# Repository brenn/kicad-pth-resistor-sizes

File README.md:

Simple PCB with PTH resistor sizes, for kicad work

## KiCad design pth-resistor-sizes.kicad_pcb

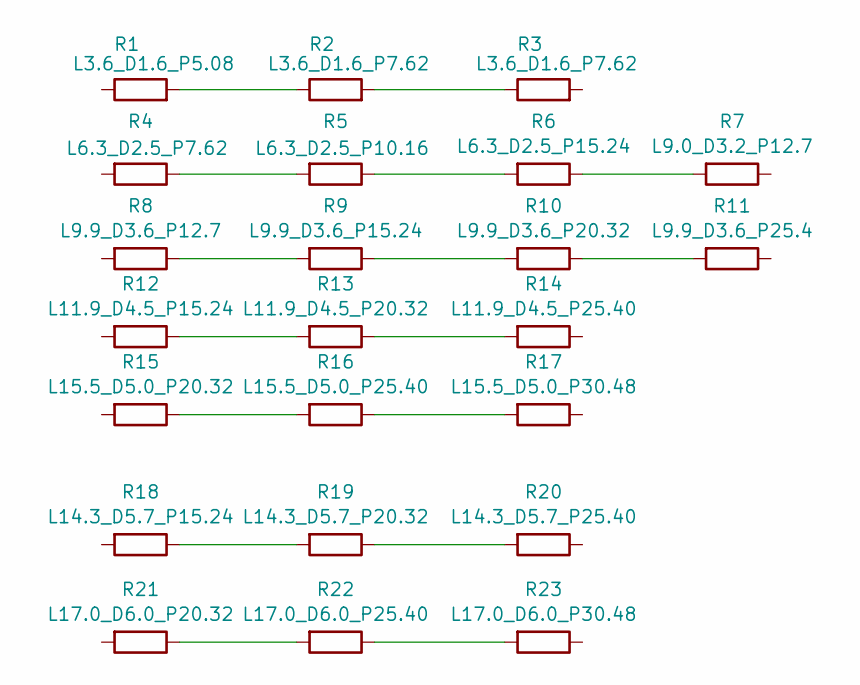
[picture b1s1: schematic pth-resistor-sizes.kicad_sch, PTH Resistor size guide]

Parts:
R1: 100k; R_Axial_DIN0204_L3.6mm_D1.6mm_P5.08mm_Horizontal
R2, R3: 100k; R_Axial_DIN0204_L3.6mm_D1.6mm_P7.62mm_Horizontal
R4: 100k; R_Axial_DIN0207_L6.3mm_D2.5mm_P7.62mm_Horizontal
R5: 100k; R_Axial_DIN0207_L6.3mm_D2.5mm_P10.16mm_Horizontal
R6: 100k; R_Axial_DIN0207_L6.3mm_D2.5mm_P15.24mm_Horizontal
R7: 100k; R_Axial_DIN0309_L9.0mm_D3.2mm_P12.70mm_Horizontal
R8: 100k; R_Axial_DIN0411_L9.9mm_D3.6mm_P12.70mm_Horizontal
R9: 100k; R_Axial_DIN0411_L9.9mm_D3.6mm_P15.24mm_Horizontal
R10: 100k; R_Axial_DIN0411_L9.9mm_D3.6mm_P20.32mm_Horizontal
R11: 100k; R_Axial_DIN0411_L9.9mm_D3.6mm_P25.40mm_Horizontal
R12: 100k; R_Axial_DIN0414_L11.9mm_D4.5mm_P15.24mm_Horizontal
R13: 100k; R_Axial_DIN0414_L11.9mm_D4.5mm_P20.32mm_Horizontal
R14: 100k; R_Axial_DIN0414_L11.9mm_D4.5mm_P25.40mm_Horizontal
R15: 100k; R_Axial_DIN0516_L15.5mm_D5.0mm_P20.32mm_Horizontal
R16: 100k; R_Axial_DIN0516_L15.5mm_D5.0mm_P25.40mm_Horizontal
R17: 100k; R_Axial_DIN0516_L15.5mm_D5.0mm_P30.48mm_Horizontal
R18: 100k; R_Axial_DIN0614_L14.3mm_D5.7mm_P15.24mm_Horizontal
R19: 100k; R_Axial_DIN0614_L14.3mm_D5.7mm_P20.32mm_Horizontal
R20: 100k; R_Axial_DIN0614_L14.3mm_D5.7mm_P25.40mm_Horizontal
R21: 100k; R_Axial_DIN0617_L17.0mm_D6.0mm_P20.32mm_Horizontal
R22: 100k; R_Axial_DIN0617_L17.0mm_D6.0mm_P25.40mm_Horizontal
R23: 100k; R_Axial_DIN0617_L17.0mm_D6.0mm_P30.48mm_Horizontal

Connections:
unnamed: R1.2, R2.1
unnamed: R2.2, R3.1
unnamed: R4.1, R5.2
unnamed: R5.1, R6.2
unnamed: R6.1, R7.2
unnamed: R8.1, R9.2
unnamed: R10.1, R11.2
unnamed: R9.1, R10.2
unnamed: R12.1, R13.2
unnamed: R13.1, R14.2
unnamed: R15.1, R16.2
unnamed: R16.1, R17.2
unnamed: R18.1, R19.2
unnamed: R19.1, R20.2
unnamed: R21.1, R22.2
unnamed: R22.1, R23.2

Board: 2 copper layers, 23 parts (0 on the bottom side), 16 nets, no tracks yet.

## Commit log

2026-03-14 initial
2026-03-14 Created README.md
2026-03-14 board image
2026-03-14 re-render
